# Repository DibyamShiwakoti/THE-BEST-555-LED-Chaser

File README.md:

# THE-BEST-555-LED-Chaser
This is my attempt at my first Hackclub starter project, the Blinky Board (also known as 555 LED chaser) that I designed using KiCad.

Parts ordered:
Blinky Board Kit (Starter Kit by HackClub) - 10$
PCB (JLCPCB) - 5.12$
Soldering Iron (link: https://www.walmart.com/ip/Soldering-Iron-Kit-Electric-60W-110V-Adjustable-Temperature-Soldering-Gun-Welding-Tools-5pcs-Replacement-Tips-and-Solder-Wire-Tube-Basic/5744425180?wmlspartner=wlpa&selectedSellerId=101270182) - 10.99$

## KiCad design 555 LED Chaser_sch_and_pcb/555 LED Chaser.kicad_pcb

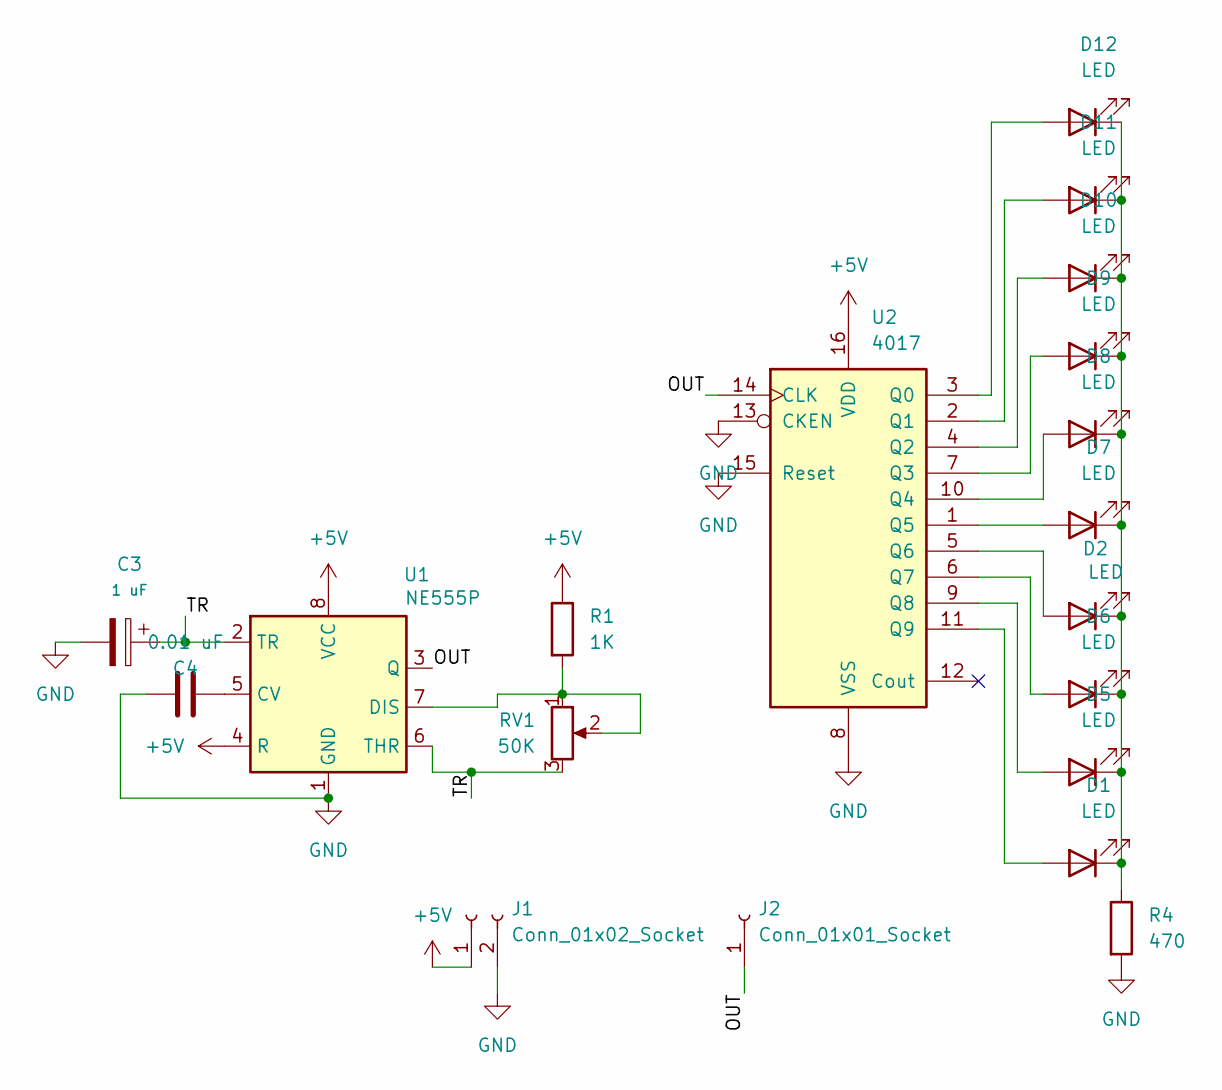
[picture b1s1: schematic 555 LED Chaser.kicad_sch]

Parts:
C3: 1 uF; CP_Radial_D5.0mm_P2.00mm
C4: 0.01 uF; C_Disc_D7.5mm_W2.5mm_P5.00mm
D1, D2, D5, D6, D7, D8, D9, D10, D11, D12: LED; LED_D3.0mm
J1: Conn_01x02_Socket; PinHeader_1x02_P2.54mm_Vertical
J2: Conn_01x01_Socket; PinHeader_1x01_P2.54mm_Vertical
R1: 1K; R_Axial_DIN0207_L6.3mm_D2.5mm_P7.62mm_Horizontal
R4: 470; R_Axial_DIN0207_L6.3mm_D2.5mm_P7.62mm_Horizontal
RV1: 50K; Potentiometer_Vishay_T93YA_Vertical
U1: NE555P; DIP-8_W7.62mm
U2: 4017; N16

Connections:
+5V: J1.1, R1.1, U1.4 (R), U1.8 (VCC), U2.16 (VDD)
/OUT: J2.1 (Pin_1_1), U1.3 (Q), U2.14 (CLK)
/TR: C3.1, RV1.3, U1.2 (TR), U1.6 (THR)
GND: C3.2, C4.2, J1.2, R4.2, U1.1 (GND), U2.8 (VSS), U2.13 (CKEN), U2.15 (Reset)
unnamed: D1.2 (A), U2.11 (Q9)
unnamed: D1.1 (K), D2.1 (K), D5.1 (K), D6.1 (K), D7.1 (K), D8.1 (K), D9.1 (K), D10.1 (K), D11.1 (K), D12.1 (K), R4.1
unnamed: D2.2 (A), U2.5 (Q6)
unnamed: D5.2 (A), U2.9 (Q8)
unnamed: D6.2 (A), U2.6 (Q7)
unnamed: D7.2 (A), U2.1 (Q5)
unnamed: D8.2 (A), U2.10 (Q4)
unnamed: D9.2 (A), U2.7 (Q3)
unnamed: D10.2 (A), U2.4 (Q2)
unnamed: D11.2 (A), U2.2 (Q1)
unnamed: D12.2 (A), U2.3 (Q0)
unnamed: C4.1, U1.5 (CV)
unnamed: R1.2, RV1.1, RV1.2, U1.7 (DIS)

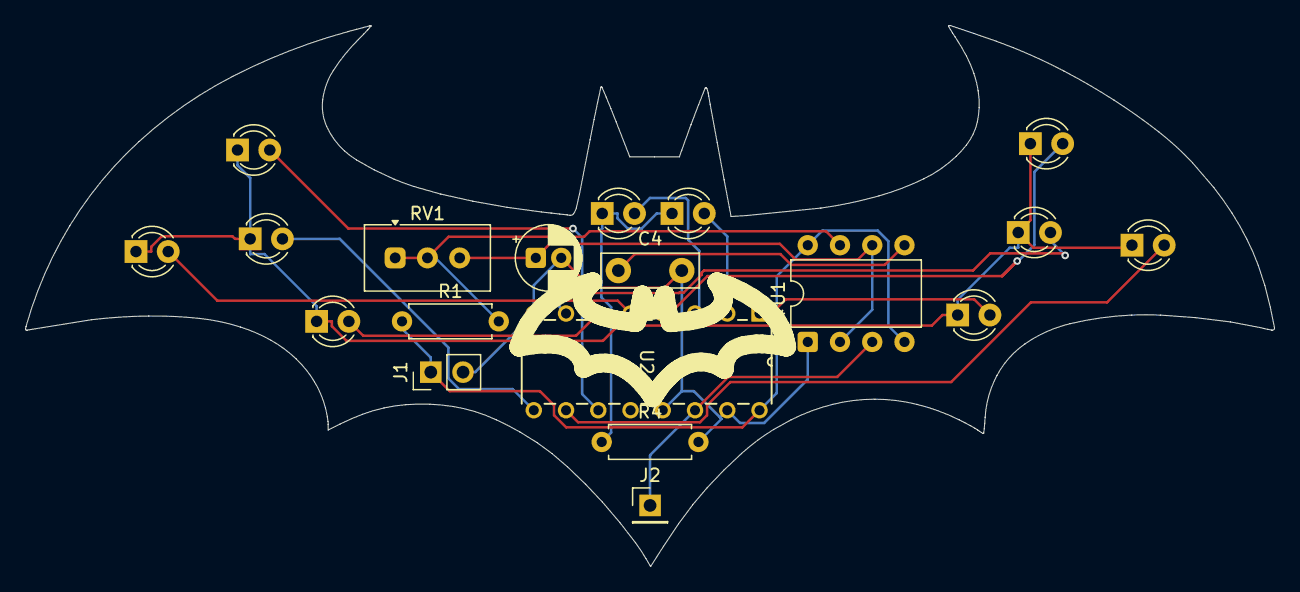
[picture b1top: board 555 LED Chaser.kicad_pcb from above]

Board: 2 copper layers, 98.4 x 42.6 mm, 19 parts (0 on the bottom side), 17 nets.
